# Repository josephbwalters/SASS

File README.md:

# SASS
Repository for all code related to UCF CECS Senior Design Project (S.A.S.S. -- Fall 2018 - Spring 2019)

[SASS Github Pages](https://josephbwalters.github.io/SASS/) - Product overview and team details!  
[UCF SASS Website](https://www.ece.ucf.edu/seniordesign/fa2018sp2019/g03/) - it is a copy of our overview site  
[All UCF Projects](https://www.ece.ucf.edu/seniordesign/projects.php) - all UCF senior design projects  

## Installation:
- Clone Repo
- Open SASS, MSS, and DSS seperately in Code Composer Studio (CCS)

## Building Software
### SASS
- Build using CCS

### MMWAVE
- Build DSS in CCS
- Then build MSS in CCS

## Flashing Firmware onto devices
*Note: This is done after building each component*
### SASS
- Using CCS and a MSP432P401R EVM (Dev. Kit) you can flash the system externally

### MMWAVE
- Take the mmwave .bin file from the MSS' Debug folder and use UniFlash to flash the mmwave EVM

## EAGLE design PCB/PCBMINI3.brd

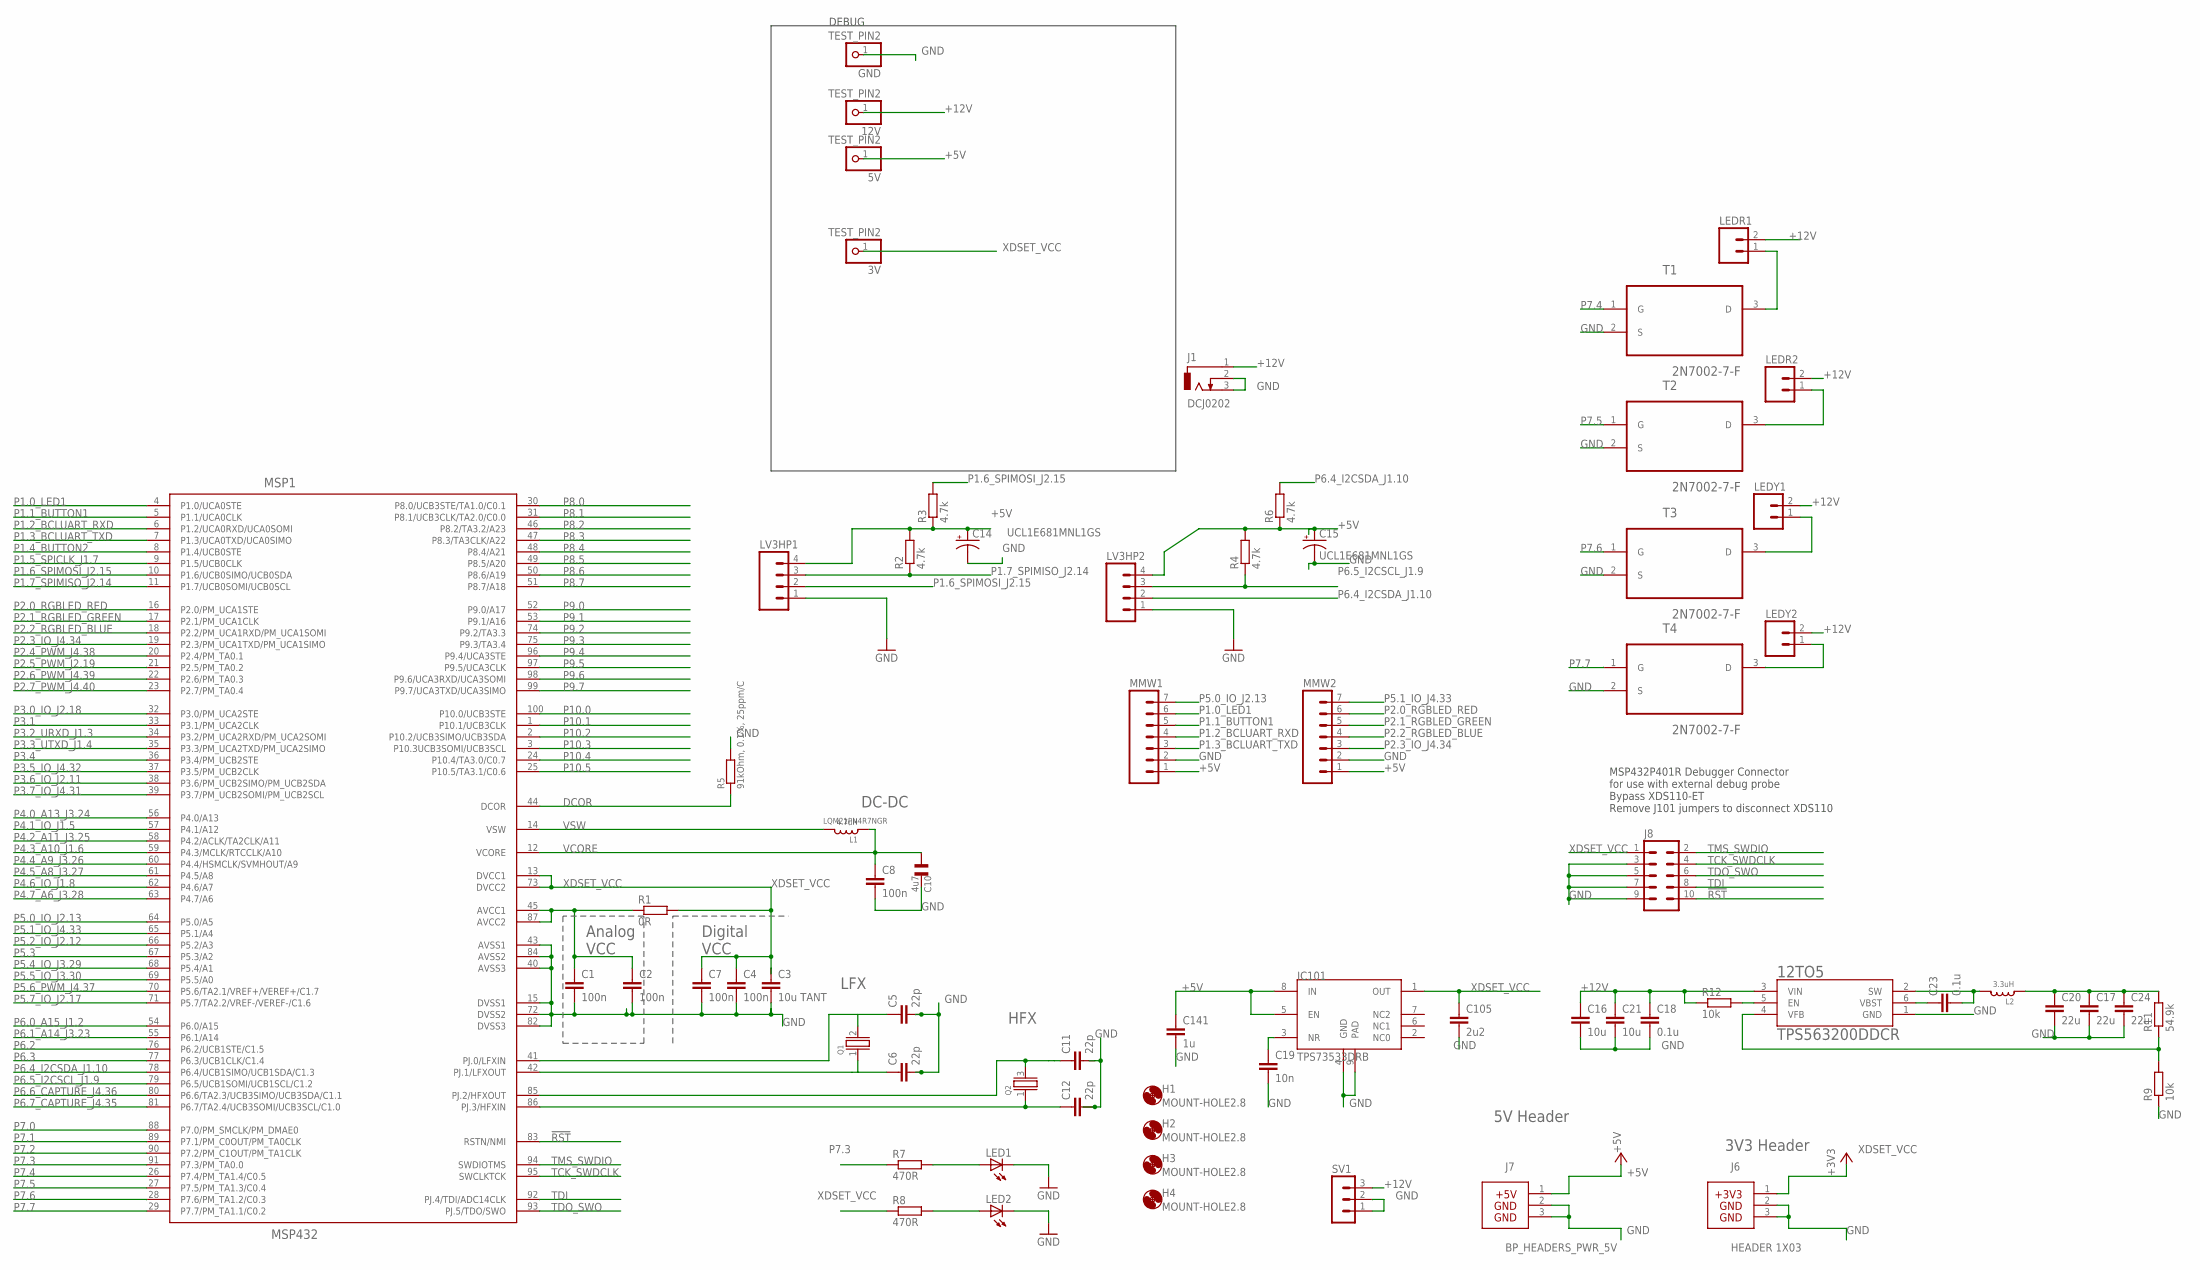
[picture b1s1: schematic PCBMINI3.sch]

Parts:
3V, 5V, 12V: TEST_PIN2; 1X01
12TO5: TPS563200DDCR; SOT95P280X110-6N
C1, C2, C4, C7, C8: 100n; C0805
C3: 10u TANT; C0805
C5, C6, C11, C12: 22p; C0805
C10: 4u7; CSMD0805
C14, C15: UCL1E681MNL1GS; CAPAE1030X1350N
C16, C21: 10u; C0805
C17, C20, C24: 22u; C0805
C18, C23: 0.1u; C0805
C19: 10n; C0603
C105: 2u2; C0603
C141: 1u; C0603
GND: TEST_PIN2; 1X01
H1, H2, H3, H4: MOUNT-HOLE2.8; 2,8
IC101: TPS73533DRB; SON8
J1: DCJ0202
J6: HEADER 1X03; 3PIN_PWR_3V3
J7: BP_HEADERS_PWR_5V; 3PIN_PWR_5V
J8: DEBUG_ARM-10; ARM-10
L1: 4.7uH; 0806
L2: 3.3uH; 0806
LED1, LED2: LED_E; LED_1206
LEDR1, LEDR2: MA02; 02PA
LEDY1, LEDY2: MA02; 02PA
LV3HP1, LV3HP2: MA04; 04PA
MMW1, MMW2: MA07; 07PA
MSP1: MSP432; PZ100
Q1: CRYSTALLF_GENERAL; LF_XTAL
Q2: CRYSTALEPSON_FA-238; FA-238
R1: 0R; R0805
R2, R3, R4, R6: 4.7k; R0805
R5: 91kOhm, 0.1%, 25ppm/C; 0805
R7, R8: 470R; R0805
R9, R12: 10k; R0805
R11: 54.9k; R0805
SV1: MA03-1
T1, T2, T3, T4: 2N7002-7-F; SOT103P240X110-3N

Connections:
!RST: J8.10, MSP1.83 (RSTN/NMI)
+5V: 5V.1, C14.A (+), C15.A (+), C141.1, IC101.5 (EN), IC101.8 (IN), J7.1, LV3HP1.4, LV3HP2.4, MMW1.1, MMW2.1, R2.2, R3.1, R4.2, R6.1
+12V: 12TO5.3 (VIN), 12V.1, C16.1, C18.1, C21.1, J1.1, LEDR1.2, LEDR2.2, LEDY1.2, LEDY2.2, R12.1, SV1.3
DCOR: MSP1.44 (DCOR), R5.1
GND: 12TO5.1 (GND), C1.2, C2.2, C3.2, C4.2, C5.2, C6.2, C7.2, C8.2, C10.2, C11.2, C12.2, C14.C (-), C15.C (-), C16.2, C17.2, C18.2, C19.2, C20.2, C21.2, C24.2, C105.2, C141.2, GND.1, IC101.4 (GND), IC101.9 (PAD), J1.2, J1.3, J6.2, J6.3, J7.2, J7.3, J8.3, J8.5, J8.7, J8.9, LED1.C, LED2.C, LV3HP1.1, LV3HP2.1, MMW1.2, MMW2.2, MSP1.15 (DVSS1), MSP1.40 (AVSS3), MSP1.43 (AVSS1), MSP1.72 (DVSS2), MSP1.82 (DVSS3), MSP1.84 (AVSS2), R5.2, R9.1, SV1.1, SV1.2, T1.2 (S), T2.2 (S), T3.2 (S), T4.2 (S)
unnamed: LEDY2.1, T4.3 (D)
unnamed: LED1.A, R7.2
unnamed: LED2.A, R8.2
unnamed: 12TO5.5 (EN), R12.2
unnamed: LEDR1.1, T1.3 (D)
unnamed: C1.1, C2.1, MSP1.45 (AVCC1), MSP1.87 (AVCC2), R1.1
unnamed: 12TO5.2 (SW), C23.2, L2.2
unnamed: C17.1, C20.1, C24.1, L2.1, R11.2
unnamed: LEDR2.1, T2.3 (D)
unnamed: C19.1, IC101.3 (NR)
unnamed: 12TO5.6 (VBST), C23.1
unnamed: 12TO5.4 (VFB), R9.2, R11.1
unnamed: C6.1, MSP1.42 (PJ.1/LFXOUT), Q1.1
unnamed: C5.1, MSP1.41 (PJ.0/LFXIN), Q1.2
P1.0_LED1: MMW1.6, MSP1.4 (P1.0/UCA0STE)
P1.1_BUTTON1: MMW1.5, MSP1.5 (P1.1/UCA0CLK)
P1.2_BCLUART_RXD: MMW1.4, MSP1.6 (P1.2/UCA0RXD/UCA0SOMI)
P1.3_BCLUART_TXD: MMW1.3, MSP1.7 (P1.3/UCA0TXD/UCA0SIMO)
P1.4_BUTTON2: MSP1.8 (P1.4/UCB0STE)
P1.5_SPICLK_J1.7: MSP1.9 (P1.5/UCB0CLK)
P1.6_SPIMOSI_J2.15: LV3HP1.2, MSP1.10 (P1.6/UCB0SIMO/UCB0SDA), R3.2
P1.7_SPIMISO_J2.14: LV3HP1.3, MSP1.11 (P1.7/UCB0SOMI/UCB0SCL), R2.1
P2.0_RGBLED_RED: MMW2.6, MSP1.16 (P2.0/PM_UCA1STE)
P2.1_RGBLED_GREEN: MMW2.5, MSP1.17 (P2.1/PM_UCA1CLK)
P2.2_RGBLED_BLUE: MMW2.4, MSP1.18 (P2.2/PM_UCA1RXD/PM_UCA1SOMI)
P2.3_IO_J4.34: MMW2.3, MSP1.19 (P2.3/PM_UCA1TXD/PM_UCA1SIMO)
P2.4_PWM_J4.38: MSP1.20 (P2.4/PM_TA0.1)
P2.5_PWM_J2.19: MSP1.21 (P2.5/PM_TA0.2)
P2.6_PWM_J4.39: MSP1.22 (P2.6/PM_TA0.3)
P2.7_PWM_J4.40: MSP1.23 (P2.7/PM_TA0.4)
P3.0_IO_J2.18: MSP1.32 (P3.0/PM_UCA2STE)
P3.1: MSP1.33 (P3.1/PM_UCA2CLK)
P3.2_URXD_J1.3: MSP1.34 (P3.2/PM_UCA2RXD/PM_UCA2SOMI)
P3.3_UTXD_J1.4: MSP1.35 (P3.3/PM_UCA2TXD/PM_UCA2SIMO)
P3.4: MSP1.36 (P3.4/PM_UCB2STE)
P3.5_IO_J4.32: MSP1.37 (P3.5/PM_UCB2CLK)
P3.6_IO_J2.11: MSP1.38 (P3.6/PM_UCB2SIMO/PM_UCB2SDA)
P3.7_IO_J4.31: MSP1.39 (P3.7/PM_UCB2SOMI/PM_UCB2SCL)
P4.0_A13_J3.24: MSP1.56 (P4.0/A13)
P4.1_IO_J1.5: MSP1.57 (P4.1/A12)
P4.2_A11_J3.25: MSP1.58 (P4.2/ACLK/TA2CLK/A11)
P4.3_A10_J1.6: MSP1.59 (P4.3/MCLK/RTCCLK/A10)
P4.4_A9_J3.26: MSP1.60 (P4.4/HSMCLK/SVMHOUT/A9)
P4.5_A8_J3.27: MSP1.61 (P4.5/A8)
P4.6_IO_J1.8: MSP1.62 (P4.6/A7)
P4.7_A6_J3.28: MSP1.63 (P4.7/A6)
P5.0_IO_J2.13: MMW1.7, MSP1.64 (P5.0/A5)
P5.1_IO_J4.33: MMW2.7, MSP1.65 (P5.1/A4)
P5.2/XT2IN: C12.1, MSP1.86 (PJ.3/HFXIN), Q2.1
P5.2_IO_J2.12: MSP1.66 (P5.2/A3)
P5.3: MSP1.67 (P5.3/A2)
P5.3/XT2OUT: C11.1, MSP1.85 (PJ.2/HFXOUT), Q2.3 (2)
P5.4_IO_J3.29: MSP1.68 (P5.4/A1)
P5.5_IO_J3.30: MSP1.69 (P5.5/A0)
P5.6_PWM_J4.37: MSP1.70 (P5.6/TA2.1/VREF+/VEREF+/C1.7)
P5.7_IO_J2.17: MSP1.71 (P5.7/TA2.2/VREF-/VEREF-/C1.6)
P6.0_A15_J1.2: MSP1.54 (P6.0/A15)
P6.1_A14_J3.23: MSP1.55 (P6.1/A14)
P6.2: MSP1.76 (P6.2/UCB1STE/C1.5)
P6.3: MSP1.77 (P6.3/UCB1CLK/C1.4)
P6.4_I2CSDA_J1.10: LV3HP2.2, MSP1.78 (P6.4/UCB1SIMO/UCB1SDA/C1.3), R6.2
P6.5_I2CSCL_J1.9: LV3HP2.3, MSP1.79 (P6.5/UCB1SOMI/UCB1SCL/C1.2), R4.1
P6.6_CAPTURE_J4.36: MSP1.80 (P6.6/TA2.3/UCB3SIMO/UCB3SDA/C1.1)
P6.7_CAPTURE_J4.35: MSP1.81 (P6.7/TA2.4/UCB3SOMI/UCB3SCL/C1.0)
P7.0: MSP1.88 (P7.0/PM_SMCLK/PM_DMAE0)
P7.1: MSP1.89 (P7.1/PM_C0OUT/PM_TA0CLK)
P7.2: MSP1.90 (P7.2/PM_C1OUT/PM_TA1CLK)
P7.3: MSP1.91 (P7.3/PM_TA0.0), R7.1
P7.4: MSP1.26 (P7.4/PM_TA1.4/C0.5), T1.1 (G)
P7.5: MSP1.27 (P7.5/PM_TA1.3/C0.4), T2.1 (G)
P7.6: MSP1.28 (P7.6/PM_TA1.2/C0.3), T3.1 (G)
P7.7: MSP1.29 (P7.7/PM_TA1.1/C0.2), T4.1 (G)
P8.0: MSP1.30 (P8.0/UCB3STE/TA1.0/C0.1)
P8.1: MSP1.31 (P8.1/UCB3CLK/TA2.0/C0.0)
P8.2: MSP1.46 (P8.2/TA3.2/A23)
P8.3: MSP1.47 (P8.3/TA3CLK/A22)
P8.4: MSP1.48 (P8.4/A21)
P8.5: MSP1.49 (P8.5/A20)
P8.6: MSP1.50 (P8.6/A19)
P8.7: MSP1.51 (P8.7/A18)
P9.0: MSP1.52 (P9.0/A17)
P9.1: MSP1.53 (P9.1/A16)
P9.2: MSP1.74 (P9.2/TA3.3)
P9.3: MSP1.75 (P9.3/TA3.4)
P9.4: MSP1.96 (P9.4/UCA3STE)
P9.5: MSP1.97 (P9.5/UCA3CLK)
P9.6: MSP1.98 (P9.6/UCA3RXD/UCA3SOMI)
P9.7: MSP1.99 (P9.7/UCA3TXD/UCA3SIMO)
P10.0: MSP1.100 (P10.0/UCB3STE)
P10.1: MSP1.1 (P10.1/UCB3CLK)
P10.2: MSP1.2 (P10.2/UCB3SIMO/UCB3SDA)
P10.3: MSP1.3 (P10.3UCB3SOMI/UCB3SCL)
P10.4: MSP1.24 (P10.4/TA3.0/C0.7)
P10.5: MSP1.25 (P10.5/TA3.1/C0.6)
TCK_SWDCLK: J8.4, MSP1.95 (SWCLKTCK)
TDI: J8.8, MSP1.92 (PJ.4/TDI/ADC14CLK)
TDO_SWO: J8.6, MSP1.93 (PJ.5/TDO/SWO)
TMS_SWDIO: J8.2, MSP1.94 (SWDIOTMS)
VCORE: C8.1, C10.1, L1.1, MSP1.12 (VCORE)
VSW: L1.2, MSP1.14 (VSW)
XDSET_VCC: 3V.1, C3.1, C4.1, C7.1, C105.1, IC101.1 (OUT), J6.1, J8.1, MSP1.13 (DVCC1), MSP1.73 (DVCC2), R1.2, R8.1
Y1: LEDY1.1, T3.3 (D)

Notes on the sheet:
LQM21PN4R7NGR
HFX
LFX
Analog
VCC
Digital
DC-DC
5V Header
MSP432P401R Debugger Connector for use with external debug probe Bypass XDS110-ET Remove J101 jumpers to disconnect XDS110
3V3 Header
DEBUG

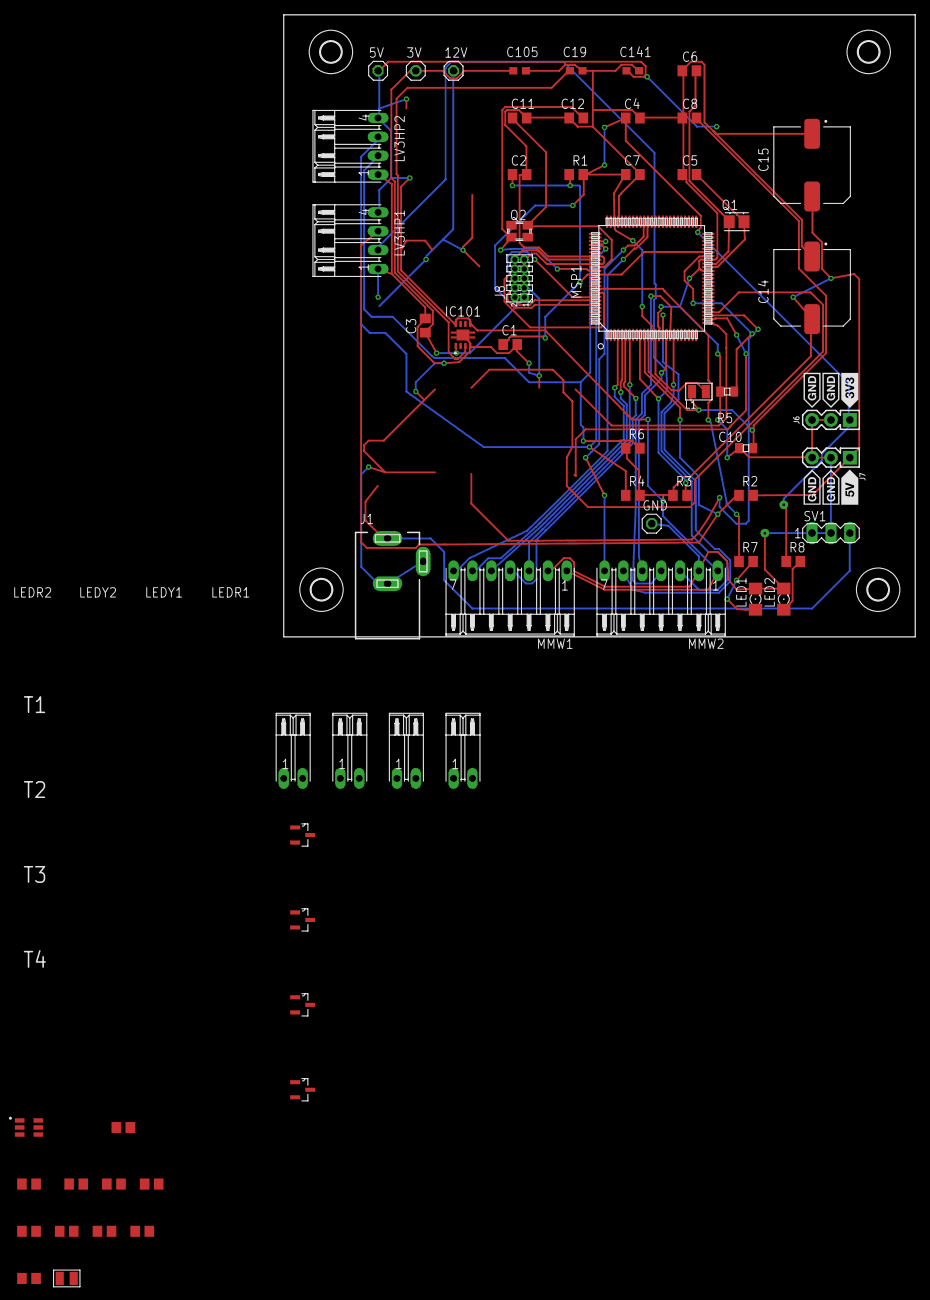
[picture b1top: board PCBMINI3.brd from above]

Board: 2 copper layers, 85.0 x 83.7 mm, 68 parts (0 on the bottom side), 48 nets.

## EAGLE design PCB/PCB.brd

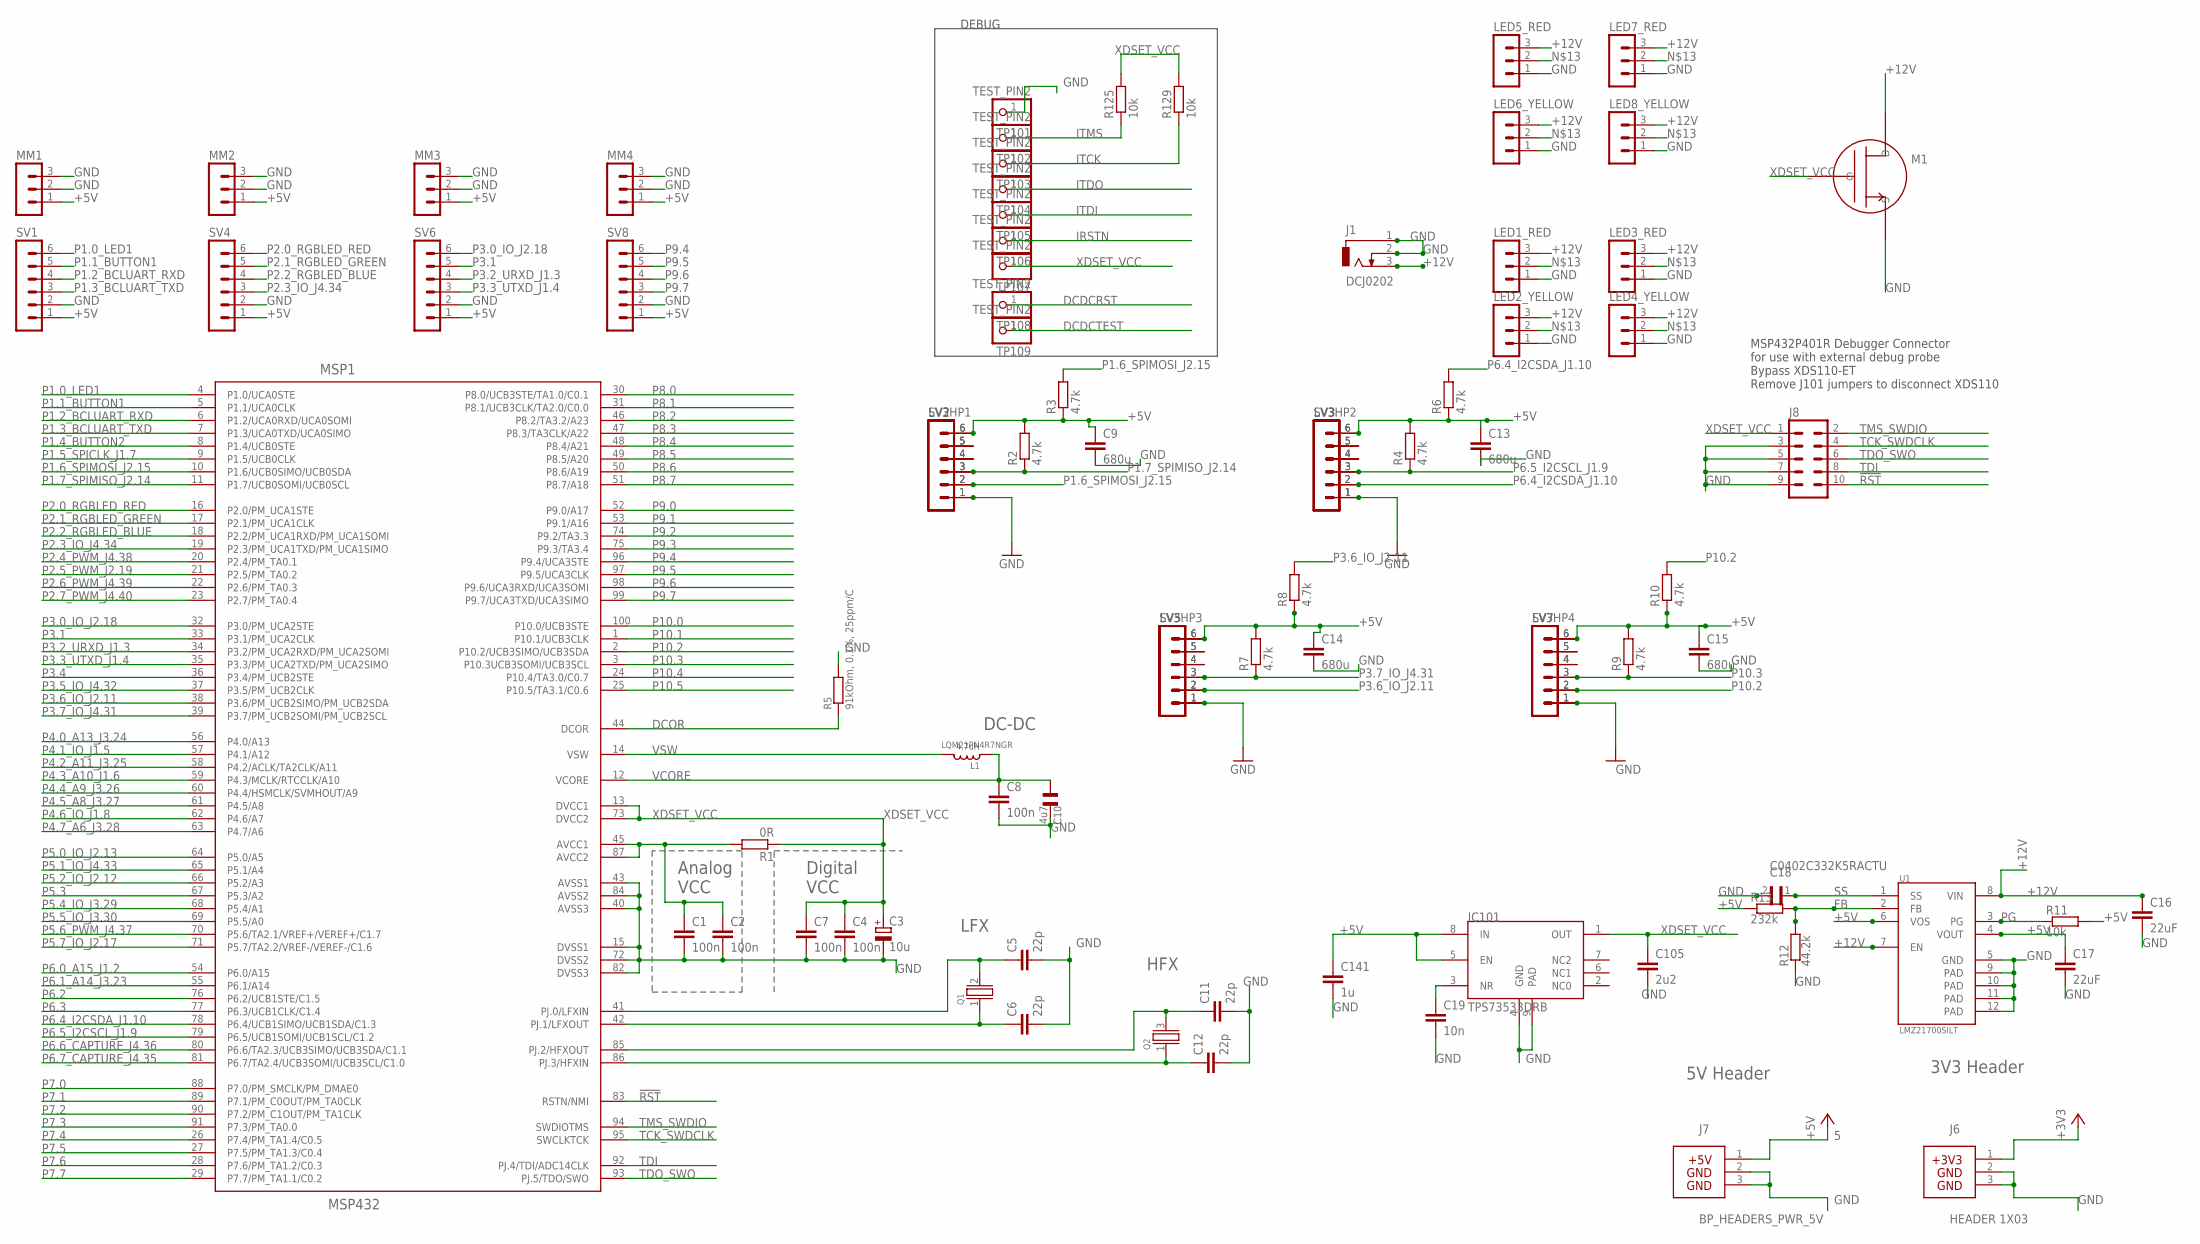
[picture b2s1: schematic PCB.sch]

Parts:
C1, C2, C4, C7, C8: 100n; 0402
C3: 10u; A/3216-18R
C5, C6, C11, C12: 22p; 0402
C9, C13, C14, C15: 680u; 0402
C10: 4u7; CSMD0805
C16, C17: 22uF; 0805
C18: C0402C332K5RACTU; CAPC1005X55N
C19: 10n; C0603
C105: 2u2; C0603
C141: 1u; C0603
IC101: TPS73533DRB; SON8
J1: DCJ0202
J6: HEADER 1X03; 3PIN_PWR_3V3
J7: BP_HEADERS_PWR_5V; 3PIN_PWR_5V
J8: DEBUG_ARM-10; ARM-10
L1: 4.7uH; 0806
LED1_RED, LED2_YELLOW, LED3_RED, LED4_YELLOW, LED5_RED, LED6_YELLOW, LED7_RED, LED8_YELLOW: MA03-1
LV3HP1, LV3HP2, LV3HP3, LV3HP4: MA06-1
MM1, MM2, MM3, MM4: MA03-1
MSP1: MSP432; PZ100
Q1: CRYSTALLF_GENERAL; LF_XTAL
Q2: CRYSTALEPSON_FA-238; FA-238
R1: 0R; 0402
R2, R3, R4, R6, R7, R8, R9, R10: 4.7k; 0402
R5: 91kOhm, 0.1%, 25ppm/C; 0805
R11: 10k; SMK
R12: 44.2k; SMK
R13: 232k; SMK
R125, R129: 10k; 0402
SV1, SV2, SV3, SV4, SV5, SV6, SV7, SV8: MA06-1
TP101, TP102, TP103, TP104, TP105, TP106, TP107, TP108, TP109: TEST_PIN2; 1X01
U1: LMZ21700SILT; DFN350X350X175-10RN

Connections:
5: J7.1
!RST: J8.10, MSP1.83 (RSTN/NMI)
+3V3: J6.1
+5V: C9.1, C13.1, C14.1, C15.1, C17.1, C141.1, IC101.5 (EN), IC101.8 (IN), LV3HP1.6, LV3HP2.6, LV3HP3.6, LV3HP4.6, MM1.1, MM2.1, MM3.1, MM4.1, R2.2, R3.1, R4.2, R6.1, R7.2, R8.1, R9.2, R10.1, R11.1, R13.2, SV1.1, SV2.6, SV3.6, SV4.1, SV5.6, SV6.1, SV7.6, SV8.1, U1.4 (VOUT), U1.6 (VOS)
+12V: C16.1, J1.3, LED1_RED.3, LED2_YELLOW.3, LED3_RED.3, LED4_YELLOW.3, LED5_RED.3, LED6_YELLOW.3, LED7_RED.3, LED8_YELLOW.3, U1.7 (EN), U1.8 (VIN)
DCDCRST: TP108.1
DCDCTEST: TP109.1
DCOR: MSP1.44 (DCOR), R5.1
FB: R12.1, R13.1, U1.2 (FB)
GND: C1.2, C2.2, C3.-, C4.2, C5.2, C6.2, C7.2, C8.2, C9.2, C10.2, C11.2, C12.2, C13.2, C14.2, C15.2, C16.2, C17.2, C18.2, C19.2, C105.2, C141.2, IC101.4 (GND), IC101.9 (PAD), J1.1, J1.2, J6.2, J6.3, J7.2, J7.3, J8.3, J8.5, J8.7, J8.9, LED1_RED.1, LED2_YELLOW.1, LED3_RED.1, LED4_YELLOW.1, LED5_RED.1, LED6_YELLOW.1, LED7_RED.1, LED8_YELLOW.1, LV3HP1.1, LV3HP2.1, LV3HP3.1, LV3HP4.1, MM1.2, MM1.3, MM2.2, MM2.3, MM3.2, MM3.3, MM4.2, MM4.3, MSP1.15 (DVSS1), MSP1.40 (AVSS3), MSP1.43 (AVSS1), MSP1.72 (DVSS2), MSP1.82 (DVSS3), MSP1.84 (AVSS2), R5.2, R12.2, SV1.2, SV2.1, SV3.1, SV4.2, SV5.1, SV6.2, SV7.1, SV8.2, TP101.1
IRSTN: TP106.1
ITCK: R129.1, TP103.1
ITDI: TP105.1
ITDO: TP104.1
ITMS: R125.1, TP102.1
unnamed: LV3HP2.4, SV3.4
unnamed: LV3HP2.5, SV3.5
unnamed: LV3HP3.4, SV5.4
unnamed: LV3HP1.4, SV2.4
unnamed: LV3HP1.5, SV2.5
unnamed: C1.1, C2.1, MSP1.45 (AVCC1), MSP1.87 (AVCC2), R1.2
unnamed: LV3HP3.5, SV5.5
unnamed: LV3HP4.4, SV7.4
unnamed: LV3HP4.5, SV7.5
unnamed: U1.5 (GND), U1.9 (PAD), U1.10 (PAD), U1.11 (PAD), U1.12 (PAD)
unnamed: C19.1, IC101.3 (NR)
unnamed: LED1_RED.2, LED2_YELLOW.2, LED3_RED.2, LED4_YELLOW.2, LED5_RED.2, LED6_YELLOW.2, LED7_RED.2, LED8_YELLOW.2
unnamed: C6.1, MSP1.42 (PJ.1/LFXOUT), Q1.1
unnamed: C5.1, MSP1.41 (PJ.0/LFXIN), Q1.2
P1.0_LED1: MSP1.4 (P1.0/UCA0STE), SV1.6
P1.1_BUTTON1: MSP1.5 (P1.1/UCA0CLK), SV1.5
P1.2_BCLUART_RXD: MSP1.6 (P1.2/UCA0RXD/UCA0SOMI), SV1.4
P1.3_BCLUART_TXD: MSP1.7 (P1.3/UCA0TXD/UCA0SIMO), SV1.3
P1.4_BUTTON2: MSP1.8 (P1.4/UCB0STE)
P1.5_SPICLK_J1.7: MSP1.9 (P1.5/UCB0CLK)
P1.6_SPIMOSI_J2.15: LV3HP1.2, MSP1.10 (P1.6/UCB0SIMO/UCB0SDA), R3.2, SV2.2
P1.7_SPIMISO_J2.14: LV3HP1.3, MSP1.11 (P1.7/UCB0SOMI/UCB0SCL), R2.1, SV2.3
P2.0_RGBLED_RED: MSP1.16 (P2.0/PM_UCA1STE), SV4.6
P2.1_RGBLED_GREEN: MSP1.17 (P2.1/PM_UCA1CLK), SV4.5
P2.2_RGBLED_BLUE: MSP1.18 (P2.2/PM_UCA1RXD/PM_UCA1SOMI), SV4.4
P2.3_IO_J4.34: MSP1.19 (P2.3/PM_UCA1TXD/PM_UCA1SIMO), SV4.3
P2.4_PWM_J4.38: MSP1.20 (P2.4/PM_TA0.1)
P2.5_PWM_J2.19: MSP1.21 (P2.5/PM_TA0.2)
P2.6_PWM_J4.39: MSP1.22 (P2.6/PM_TA0.3)
P2.7_PWM_J4.40: MSP1.23 (P2.7/PM_TA0.4)
P3.0_IO_J2.18: MSP1.32 (P3.0/PM_UCA2STE), SV6.6
P3.1: MSP1.33 (P3.1/PM_UCA2CLK), SV6.5
P3.2_URXD_J1.3: MSP1.34 (P3.2/PM_UCA2RXD/PM_UCA2SOMI), SV6.4
P3.3_UTXD_J1.4: MSP1.35 (P3.3/PM_UCA2TXD/PM_UCA2SIMO), SV6.3
P3.4: MSP1.36 (P3.4/PM_UCB2STE)
P3.5_IO_J4.32: MSP1.37 (P3.5/PM_UCB2CLK)
P3.6_IO_J2.11: LV3HP3.2, MSP1.38 (P3.6/PM_UCB2SIMO/PM_UCB2SDA), R8.2, SV5.2
P3.7_IO_J4.31: LV3HP3.3, MSP1.39 (P3.7/PM_UCB2SOMI/PM_UCB2SCL), R7.1, SV5.3
P4.0_A13_J3.24: MSP1.56 (P4.0/A13)
P4.1_IO_J1.5: MSP1.57 (P4.1/A12)
P4.2_A11_J3.25: MSP1.58 (P4.2/ACLK/TA2CLK/A11)
P4.3_A10_J1.6: MSP1.59 (P4.3/MCLK/RTCCLK/A10)
P4.4_A9_J3.26: MSP1.60 (P4.4/HSMCLK/SVMHOUT/A9)
P4.5_A8_J3.27: MSP1.61 (P4.5/A8)
P4.6_IO_J1.8: MSP1.62 (P4.6/A7)
P4.7_A6_J3.28: MSP1.63 (P4.7/A6)
P5.0_IO_J2.13: MSP1.64 (P5.0/A5)
P5.1_IO_J4.33: MSP1.65 (P5.1/A4)
P5.2/XT2IN: C12.1, MSP1.86 (PJ.3/HFXIN), Q2.1
P5.2_IO_J2.12: MSP1.66 (P5.2/A3)
P5.3: MSP1.67 (P5.3/A2)
P5.3/XT2OUT: C11.1, MSP1.85 (PJ.2/HFXOUT), Q2.3 (2)
P5.4_IO_J3.29: MSP1.68 (P5.4/A1)
P5.5_IO_J3.30: MSP1.69 (P5.5/A0)
P5.6_PWM_J4.37: MSP1.70 (P5.6/TA2.1/VREF+/VEREF+/C1.7)
P5.7_IO_J2.17: MSP1.71 (P5.7/TA2.2/VREF-/VEREF-/C1.6)
P6.0_A15_J1.2: MSP1.54 (P6.0/A15)
P6.1_A14_J3.23: MSP1.55 (P6.1/A14)
P6.2: MSP1.76 (P6.2/UCB1STE/C1.5)
P6.3: MSP1.77 (P6.3/UCB1CLK/C1.4)
P6.4_I2CSDA_J1.10: LV3HP2.2, MSP1.78 (P6.4/UCB1SIMO/UCB1SDA/C1.3), R6.2, SV3.2
P6.5_I2CSCL_J1.9: LV3HP2.3, MSP1.79 (P6.5/UCB1SOMI/UCB1SCL/C1.2), R4.1, SV3.3
P6.6_CAPTURE_J4.36: MSP1.80 (P6.6/TA2.3/UCB3SIMO/UCB3SDA/C1.1)
P6.7_CAPTURE_J4.35: MSP1.81 (P6.7/TA2.4/UCB3SOMI/UCB3SCL/C1.0)
P7.0: MSP1.88 (P7.0/PM_SMCLK/PM_DMAE0)
P7.1: MSP1.89 (P7.1/PM_C0OUT/PM_TA0CLK)
P7.2: MSP1.90 (P7.2/PM_C1OUT/PM_TA1CLK)
P7.3: MSP1.91 (P7.3/PM_TA0.0)
P7.4: MSP1.26 (P7.4/PM_TA1.4/C0.5)
P7.5: MSP1.27 (P7.5/PM_TA1.3/C0.4)
P7.6: MSP1.28 (P7.6/PM_TA1.2/C0.3)
P7.7: MSP1.29 (P7.7/PM_TA1.1/C0.2)
P8.0: MSP1.30 (P8.0/UCB3STE/TA1.0/C0.1)
P8.1: MSP1.31 (P8.1/UCB3CLK/TA2.0/C0.0)
P8.2: MSP1.46 (P8.2/TA3.2/A23)
P8.3: MSP1.47 (P8.3/TA3CLK/A22)
P8.4: MSP1.48 (P8.4/A21)
P8.5: MSP1.49 (P8.5/A20)
P8.6: MSP1.50 (P8.6/A19)
P8.7: MSP1.51 (P8.7/A18)
P9.0: MSP1.52 (P9.0/A17)
P9.1: MSP1.53 (P9.1/A16)
P9.2: MSP1.74 (P9.2/TA3.3)
P9.3: MSP1.75 (P9.3/TA3.4)
P9.4: MSP1.96 (P9.4/UCA3STE), SV8.6
P9.5: MSP1.97 (P9.5/UCA3CLK), SV8.5
P9.6: MSP1.98 (P9.6/UCA3RXD/UCA3SOMI), SV8.4
P9.7: MSP1.99 (P9.7/UCA3TXD/UCA3SIMO), SV8.3
P10.0: MSP1.100 (P10.0/UCB3STE)
P10.1: MSP1.1 (P10.1/UCB3CLK)
P10.2: LV3HP4.2, MSP1.2 (P10.2/UCB3SIMO/UCB3SDA), R10.2, SV7.2
P10.3: LV3HP4.3, MSP1.3 (P10.3UCB3SOMI/UCB3SCL), R9.1, SV7.3
P10.4: MSP1.24 (P10.4/TA3.0/C0.7)
P10.5: MSP1.25 (P10.5/TA3.1/C0.6)
PG: R11.2, U1.3 (PG)
SS: C18.1, U1.1 (SS)
TCK_SWDCLK: J8.4, MSP1.95 (SWCLKTCK)
TDI: J8.8, MSP1.92 (PJ.4/TDI/ADC14CLK)
TDO_SWO: J8.6, MSP1.93 (PJ.5/TDO/SWO)
TMS_SWDIO: J8.2, MSP1.94 (SWDIOTMS)
VCORE: C8.1, C10.1, L1.1, MSP1.12 (VCORE)
VSW: L1.2, MSP1.14 (VSW)
XDSET_VCC: C3.+, C4.1, C7.1, C105.1, IC101.1 (OUT), J8.1, MSP1.13 (DVCC1), MSP1.73 (DVCC2), R1.1, R125.2, R129.2, TP107.1

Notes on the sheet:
LQM21PN4R7NGR
HFX
LFX
Analog
VCC
Digital
DC-DC
5V Header
MSP432P401R Debugger Connector for use with external debug probe Bypass XDS110-ET Remove J101 jumpers to disconnect XDS110
3V3 Header
DEBUG

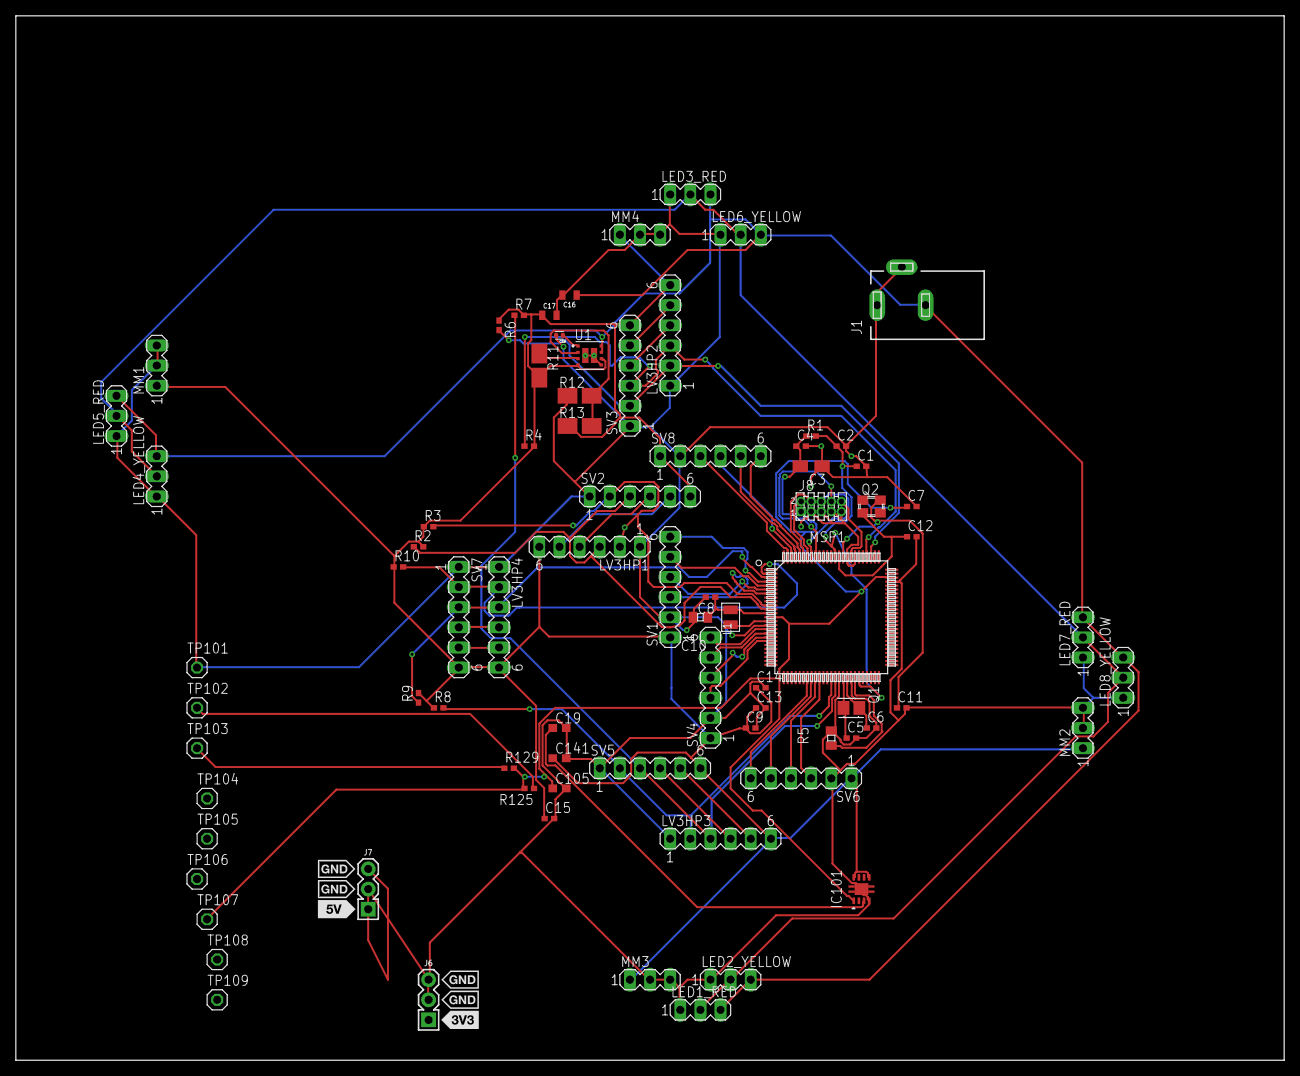
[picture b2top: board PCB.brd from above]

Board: 2 copper layers, 160.0 x 131.8 mm, 79 parts (0 on the bottom side), 57 nets.

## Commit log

2018-11-12 Added design_artifacts directory
2018-11-12 Added deployment diagram
2018-11-12 Added Joseph's state diagram
2018-11-12 Added component and large_class diagrams and modified deployment diagram
2018-11-12 Added oc and tlc class diagrams
2018-11-14 Updated deployment and component diagrams
2018-11-16 Updated OC class diagram
2018-11-16 Updated OC and TLC class diagrams
2018-11-16 Updated TLC class diagram
2018-11-25 Added sequence diagram
2018-11-26 Updated sequence diagram
2018-11-26 Added OC and TLC state transition diagrams
2018-11-26 Added First PCB
2018-11-28 Updated PCB Schematic
2018-12-21 Removed PCB schematic from develop branch
2018-12-21 Added framework for files in CCS
2018-12-22 Ignored build files, Updated include
2019-01-10 Added TLC init code
2019-01-11 Started fixing C++ files
2019-01-11 Finished fixing code
2019-01-11 Added board headers
2019-01-11 Modified includes
2019-01-11 Changed radar stuff
2019-01-11 Finished RADAR headers for greenboard
2019-01-11 Added LiDAR headers
2019-01-11 Added SCL naming to LiDAR headers
2019-01-11 Hotfix: SDC/SCL switched by accident
2019-01-11 Modified RedBoard.h
2019-01-11 Updated gitignore
2019-01-11 Removed weird PCB file that got kept by accident on my system
2019-01-15 Added LIDARLite_v3HP Arduino library files as basis for MSP432 adaption
2019-01-15 Commented out Arduino dependencies in LIDARLite_v3HP files
2019-01-15 Added lidarlite stuff
2019-01-15 Found energia stuff
2019-01-15 Pushing modification to util files, now superceded.
2019-01-15 Added and began modification of Energia files.
2019-01-17 Resolved issues importing Energia libraries.
2019-01-21 Scrapping Energia libraries and beginning anew.
2019-01-21 Removed LIDAR-Lite libraries and associated files.
2019-01-22 Added Lidar class.
2019-01-22 Refactored Lidar and Radar classes as multitons.
2019-01-22 Updated Lidar and Radar classes to include static methods and members.
2019-01-22 Updated Lidar and Radar classes.
2019-01-22 Added most of lidar code, read/write needs to be implemented
2019-01-22 Made minor changes to Lidar class to allow project to build.
2019-01-22 Made minor naming update to Lidar class.
2019-01-22 Added template read/write code, cleaned function calls
2019-01-22 Implemented read() and write() methods in Lidar class.
2019-01-23 Implemented get_velocity() method in Lidar class.
2019-01-24 Added basic test_lidar() thread to application.
2019-01-24 Fixed read/write issues
2019-01-24 Added logger and modified some lidar code
2019-01-24 updated logging
2019-01-24 Fixed hex formatting
2019-01-25 Refactoring I2C code.
2019-01-25 Modified I2C configuration.
2019-01-29 Reconstructed CCS project to base existing code on latest libraries.
2019-01-31 Better lidar and things
2019-02-01 Modified demo thread for light activation via LiDAR.
2019-02-01 Refactored lights
2019-02-01 Added onboard light toggle
2019-02-01 Tweaks for demo
2019-02-02 Changed traffic light pins for demo.
2019-02-04 Added mosfetToggleThread.
2019-02-05 Modified mosfetToggleThread.
2019-02-05 Refactored one last time
2019-02-18 Committed latest changes to SASS main.
2019-02-19 Add mmwave demo code with bin files
2019-02-19 Modified SASS.cpp for demo.
2019-02-19 Modified system files.
2019-02-19 Refactored Lidar class to better parallel Radar class.
2019-02-19 Added to Radar class to implement RADAR access.
2019-02-19 Refactored RedBoard.h.
2019-02-19 Refactored existing demo/test threads and implemented radarTestThread.
2019-02-19 Continued clean up of Lidar class.
2019-02-19 Continued implementation of RADAR access in Radar class.
2019-02-20 Fixed SPI access issues and added yields to allow for multiple thread execution.
2019-02-21 Remove logger, add docs, optimize Lidar and Radar
2019-02-21 Add style-guide for us
2019-02-21 Replaced reference to deprecated POSIX module in SASS.cfg with reference to updated module.
2019-02-21 Update style-guide
2019-02-21 Revert "Cleanup and docs"
2019-02-22 Modified SASS main and Radar class to support SPI software testing.
2019-02-26 Began further implementation of Scheduler and created Scheduler thread.
2019-02-28 Made further additions to Classifier and Scheduler classes.
2019-03-01 Converted Scheduler into a singleton class.
2019-03-01 Add function to do spi read/write
2019-03-01 Clean file imports
2019-03-07 Added descriptive header to top of each file, continued clean up of multiple classes, added get_data() method to Radar class, and fixed inheritance of Vehicle class from DetectedObject class.
2019-03-07 Update headers, remove UCF naming, remove useless READMEs
2019-03-07 Added primitive HWI functionality.
2019-03-09 Init website portion of the project
2019-03-12 Fixed memory leak issues with Classifier thread generation, added to Classifier thread, and added track() method to Classifier class.
2019-03-14 Added to Classifier and Scheduler logic, added timer to Scheduler thread, and removed test print thread.
2019-03-15 Resolved access violation issues, corrected light cues, added delays to Scheduler thread, and prepared Classifier and Scheduler classes for demo.
2019-03-16 Corrected .gitignore file.
2019-03-19 Added hold to schedule sequence.
2019-03-21 Got mmwave to sense distances and velocities accurately
2019-03-21 Added library changes
2019-03-22 Added basic triggering of GPIO to process_objects function and included pin mapping.
2019-03-28 Resolved LiDAR access conflict and queue capacity issue; fixed init lighting in Lights class; cleaned up SASS.cpp and Scheduler class.
2019-03-28 Improved naming, organization, and performance across classes. Refactored Lidar, Radar, and dependent classes for consistent use of Directions enum.
2019-03-31 Implemented flashing yellow, fixed emergency HWI ISR, and created Control class while adding preliminary SWI functionality.
2019-04-01 Setup template for website
2019-04-02 Modified GPIO configuration of mmWave pins on PCB to set pins as normal input and raise interrupts on high.
2019-04-02 Added set_all() method to Lights class to allow triggering of all lights at the same time.
2019-04-02 Fixed system failure interrupt, implemented Timer32 for precise timing in ISRs, and changed MSP type include to use ifndef.
2019-04-04 Modified GPIO configuration and attempted to troubleshoot GPIO HWI issues.
2019-04-04 Fixed issues
2019-04-04 Set red off, when toggling yellow
2019-04-05 Cleaned up code and refactored Lidar class to allow finer control.
2019-04-05 Added emergency failure interrupts
2019-04-06 mmwave device is stable and works now
2019-04-08 Moved original design artifacts to new 'original' subdirectory and created copies in new 'revised' subdirectory.
2019-04-08 Updated radar code
2019-04-10 Updated deployment diagram and added simplified version for conference paper.
2019-04-11 Updated artifacts
2019-04-11 Made minor changes to hwi callback
2019-04-11 Cleaned up code
2019-04-11 Commented out test thread for radar
2019-04-11 Exported new JPEGs and modified component and deployment diagrams.
2019-04-13 Changed default distance back to a distinct value.
2019-04-13 Cleaned up multiple classes. Removed velocity() method from Lidar class. Removed mutex from Scheduler class.
2019-04-13 Updated OC and TLC class diagrams.
2019-04-15 Updated OC class diagram and OC state transition diagram.
2019-04-16 Updated OD/OC state transition diagram (and renamed).
2019-04-18 Ensured existence of OD/OC state transition diagram.
2019-04-19 Added photos
2019-04-19 Pushed final changes
2019-04-19 Renamed team member pictures.
2019-04-19 Added cropped photos of team.
2019-04-19 Site layout partially done
2019-04-19 Added more pictures for scrolling pane.
2019-04-20 Added features, team, and some other info
2019-04-22 Added all of the photos
2019-04-22 Update full seq. diagram
2019-04-22 Update tlc state transition diagram
2019-04-22 Update seq. diag
2019-04-22 Fixed merge conflict with OC class diagram, refactored LLHA class diagram.
2019-04-22 Moved site to docs folder
2019-04-22 Messing with site dir
2019-04-22 Made final updates to sequence diagram and TLC state transition diagram files.
2019-04-22 Forgot to push code when I had docs in site
2019-04-22 Making docs open in new tab, forgot to push it earlier
2019-04-23 Pushing final radar code
2021-02-01 Add links to README

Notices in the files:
parts and their libraries:
SparkFun-Capacitors: Licensing: Creative Commons ShareAlike 4.0 International - https://creativecommons.org/licenses/by-sa/4.0
